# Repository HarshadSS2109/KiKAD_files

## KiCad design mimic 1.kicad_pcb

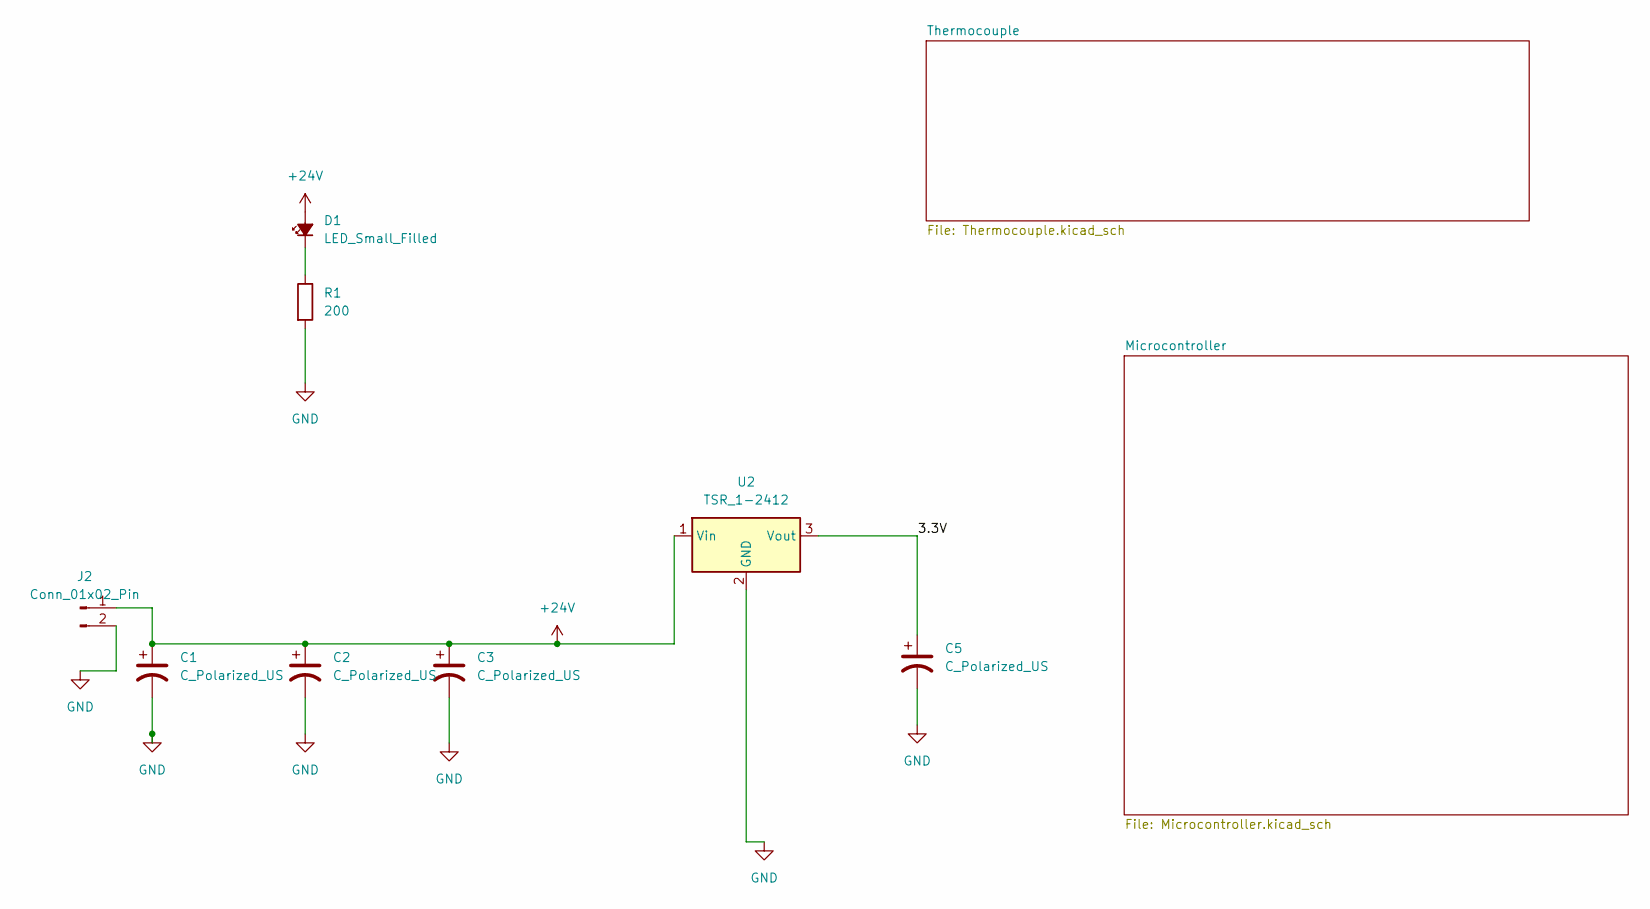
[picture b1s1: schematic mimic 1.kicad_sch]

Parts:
C1, C2, C3, C5: C_Polarized_US; CP_Elec_6.3x5.2
D1: LED_Small_Filled; LED_0402_1005Metric
J2: Conn_01x02_Pin; PhoenixContact_MC_1,5_2-G-3.5_1x02_P3.50mm_Horizontal
R1: 200; R_0603_1608Metric_Pad0.98x0.95mm_HandSolder
U2: TSR_1-2412; Converter_DCDC_TRACO_TSR-1_THT

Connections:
+24V: C1.1, C2.1, C3.1, D1.2 (A), J2.1, U2.1 (Vin)
/3.3V: C5.1, U2.3 (Vout)
GND: C1.2, C2.2, C3.2, C5.2, J2.2, R1.2, U2.2 (GND)
unnamed: D1.1 (K), R1.1

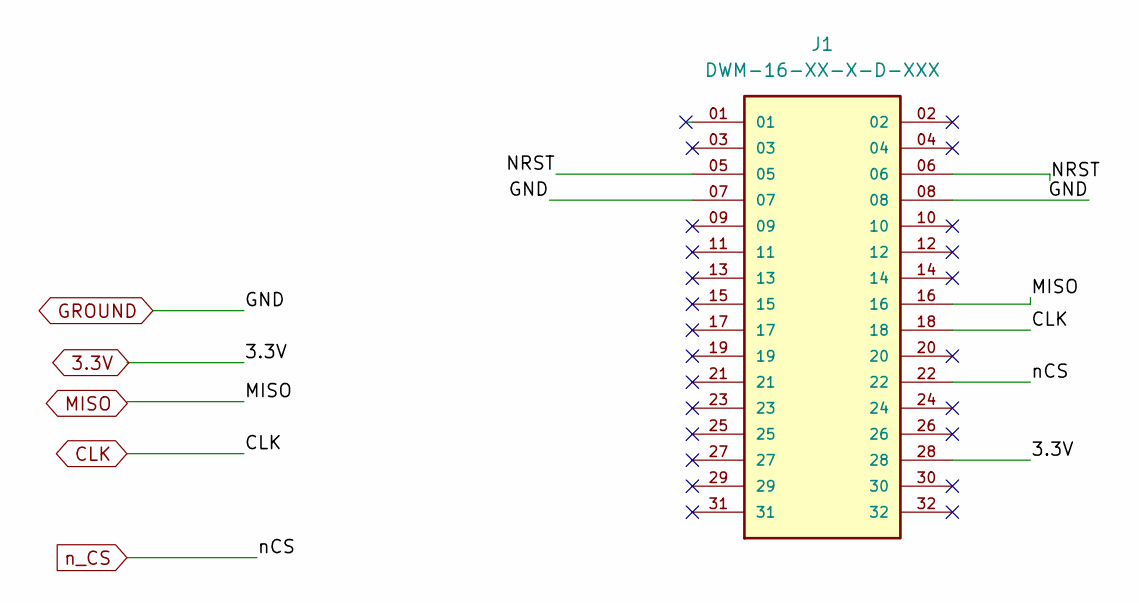
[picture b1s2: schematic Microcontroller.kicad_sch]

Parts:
J1: DWM-16-XX-X-D-XXX; SAMTEC_DWM-16-XX-X-D-XXX; PARTREV 01-31-94

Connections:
3.3V: J1.28; also elsewhere on the board
/Microcontroller/NRST: J1.05, J1.06
CLK: J1.18; also elsewhere on the board
GROUND: J1.07, J1.08; also elsewhere on the board
MISO: J1.16; also elsewhere on the board
n_CS: J1.22; also elsewhere on the board

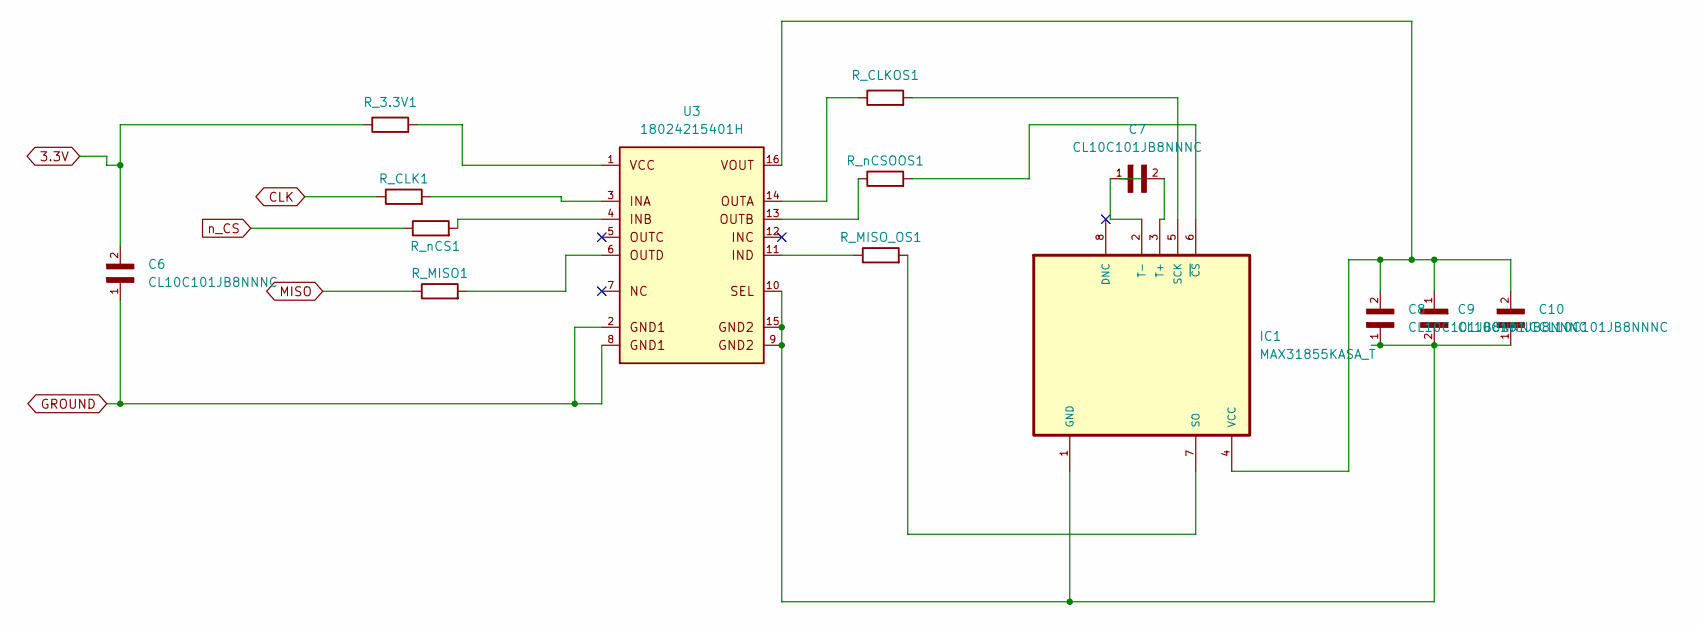
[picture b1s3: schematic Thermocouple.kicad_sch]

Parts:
C6, C7, C8, C9, C10: CL10C101JB8NNNC; CAPC1608X90N
IC1: MAX31855KASA_T; SOIC127P600X175-8N
R_3.3V1: 20; R_0603_1608Metric_Pad0.98x0.95mm_HandSolder
R_CLK1: 20; R_0603_1608Metric_Pad0.98x0.95mm_HandSolder
R_CLKOS1: 20; R_0603_1608Metric_Pad0.98x0.95mm_HandSolder
R_MISO1: 20; R_0603_1608Metric_Pad0.98x0.95mm_HandSolder
R_MISO_OS1: 20; R_0603_1608Metric_Pad0.98x0.95mm_HandSolder
R_nCS1: 20; R_0603_1608Metric_Pad0.98x0.95mm_HandSolder
R_nCSOOS1: 20; R_0603_1608Metric_Pad0.98x0.95mm_HandSolder
U3: 18024215401H; WPME-CDIP_SOIC16; PART-NUMBER 18024215401H

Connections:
3.3V: C6.2, R_3.3V1.1; also elsewhere on the board
CLK: R_CLK1.1; also elsewhere on the board
GROUND: C6.1, U3.2, U3.8; also elsewhere on the board
MISO: R_MISO1.1; also elsewhere on the board
unnamed: C8.1, C9.2, C10.1, IC1.1 (GND), U3.9, U3.10, U3.15
unnamed: IC1.5 (SCK), R_CLKOS1.2
unnamed: IC1.7 (SO), R_MISO_OS1.2
unnamed: C7.2, IC1.3 (T+)
unnamed: C7.1, IC1.2 (T-)
unnamed: C8.2, C9.1, C10.2, IC1.4 (VCC), U3.16
unnamed: IC1.6 (~CS), R_nCSOOS1.2
unnamed: R_3.3V1.2, U3.1
unnamed: R_CLK1.2, U3.3
unnamed: R_CLKOS1.1, U3.14
unnamed: R_MISO1.2, U3.6
unnamed: R_MISO_OS1.1, U3.11
unnamed: R_nCS1.2, U3.4
unnamed: R_nCSOOS1.1, U3.13
n_CS: R_nCS1.1; also elsewhere on the board

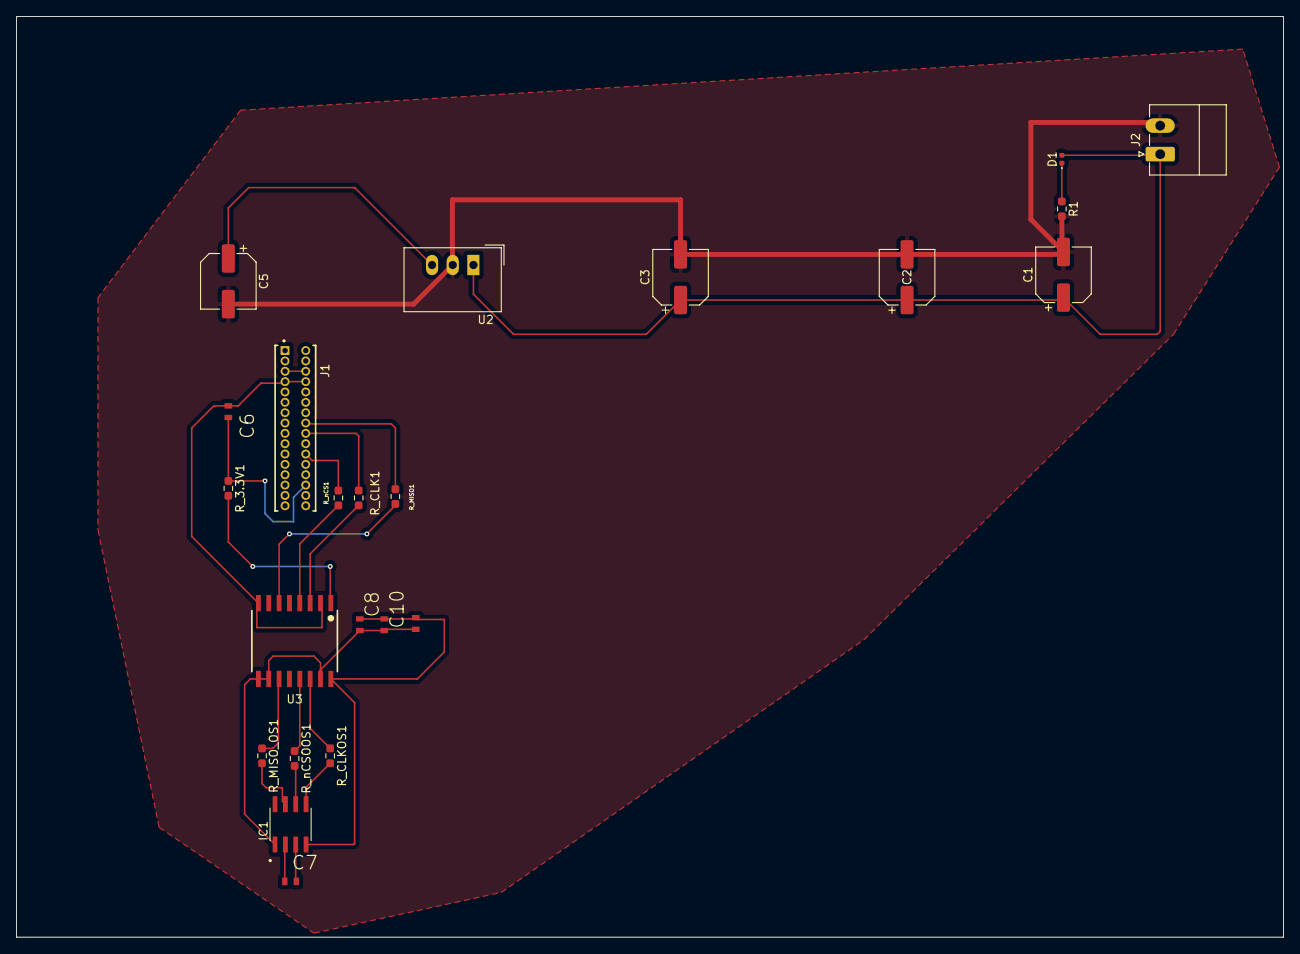
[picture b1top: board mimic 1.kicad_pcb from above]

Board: 2 copper layers, 155.5 x 113.0 mm, 23 parts (0 on the bottom side), 24 nets.

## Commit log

2025-03-06 Add files via upload
    Helo
